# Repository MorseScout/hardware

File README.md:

# Morse Scout custom I/O PCB v1.2

This directory contains the current custom I/O board for Morse Scout. It is
designed for the Elecrow CrowPanel Advanced 7-inch ESP32-P4 host board (PCB
V1.1). PCB revision 1.2 was fabricated from the included Gerber package,
passed bring-up and functional testing, and is used in the current Morse Scout
build.

## Current design

- `J1`: 2x12, 2.54 mm, pin-for-pin connection to Elecrow expansion header
  `J7`. Pins 2, 4, and 6 carry 5 V on the host and are intentionally not
  connected on the custom PCB.
- `J5`-`J7`: three switched TRS Morse-key inputs. Tip and ring are independent
  active-low contacts to ground.
- `ENC1`: rotary encoder A/B signals and push switch.
- `RV1`: 10 kOhm linear volume potentiometer. `R1/C1` form the 1 kOhm/100 nF
  ADC filter.
- `SW1`: active-low sleep/wake button with the 10 kOhm `R2` pull-up.
- `U1`: DS3231 real-time-clock module with battery backup.
- `J8`: four-position HY2.0 I2C connector (`ZX-HY2.0-4PZZ`) between
  the Elecrow board and `U1`.
- `J4`: two-wire Elecrow left-speaker input. Both conductors belong to the
  bridge-tied speaker output; neither conductor is ground.
- `J2`: switched 3.5 mm audio jack.
- `J3`: two-wire internal-speaker connector. Inserting a plug in `J2` opens
  the feed to the internal speaker.

## Opening the project

Use KiCad 10 and open `morse_scout_custom_io_elecrow.kicad_pro`. The project
library tables use `${KIPRJMOD}`, so the included `Libraries` directory is
found without machine-specific paths. A normal KiCad 10 installation is also
required for the standard KiCad symbols, footprints, and 3D models.

The project-local `MorseScout` symbol and footprint libraries contain the
custom parts required to edit and fabricate the board. Their pad and drill
geometry is based on the tested PCB v1.2 design.

## Optional third-party 3D models

This repository does **not** redistribute third-party SamacSys/Component
Search Engine symbols, footprints, or 3D models. The custom symbols and
fabrication-tested footprints needed to edit the project are included. The
footprints contain optional 3D-model references through the
`MORSESCOUT_3DMODEL_DIR` KiCad path variable, but the referenced model files
are intentionally omitted from this public repository.

To enable a fully populated local 3D view, create a directory for the
downloaded models and add this entry in **KiCad > Preferences > Configure
Paths**:

| Name | Value |
| --- | --- |
| `MORSESCOUT_3DMODEL_DIR` | Absolute path to your local model directory |

Use the filenames shown below. If the variable or a model is absent, KiCad may
report a missing model and omit that component from the 3D Viewer. This does
not affect pads, drills, copper, routing, DRC geometry, Gerbers, or other
fabrication data.

Optional vendor CAD data can be obtained from
[SamacSys Component Search Engine](https://componentsearchengine.com/). Search
for the exact manufacturer part number:

| Part | Expected filename | CAD-model search |
| --- | --- | --- |
| Kycon `STX-3120-5B-701C` audio jack | `STX-3120-5B-701C.stp` | [Search](https://componentsearchengine.com/search?term=STX-3120-5B-701C) |
| Bourns `PTV09A-4030F-B103` potentiometer | `PTV09A-4030F-B103.stp` | [Search](https://componentsearchengine.com/search?term=PTV09A-4030F-B103) |
| Omron `B3F-4050` pushbutton | `B3F-4050.stp` | [Search](https://componentsearchengine.com/search?term=B3F-4050) |
| Bourns `PEC11R-4230F-S0024` encoder | `PEC11R-4230F-S0024.stp` | [Search](https://componentsearchengine.com/search?term=PEC11R-4230F-S0024) |
| DS3231 RTC module | `DS3231-RTC-V3.step` | Based on the [DS3231 RTC Module model on GrabCAD](https://grabcad.com/library/ds3231-rtc-module-1) |
| Megastar `ZX-HY2.0-4PZZ` four-position HY2.0 connector | `CONN-TH_4P-P2.00_HX20020-4A_2.step` | [LCSC C7429580](https://www.lcsc.com/product-detail/C7429580.html) |

Availability differs by part: the service may offer a direct download or a
model-request workflow, and an account may be required. Review and accept the
provider's current terms before downloading. Keep downloaded files outside
this repository unless their license expressly permits redistribution.

Do not replace the included footprints merely to obtain a 3D model: the
included pad and drill geometry is the fabrication-tested v1.2 geometry. If an
external footprint is substituted, verify its pad numbers, hole sizes,
spacing, and mechanical clearances before manufacturing.

The fitted encoder is `PEC11R-4230F-S0024`. Its PCB mounting geometry is the
same as the shorter-shaft `PEC11R-4220F-S0024`; the project and sourcing links
use the fitted 4230F manufacturer part number.

## Release files

- KiCad source: `morse_scout_custom_io_elecrow.kicad_sch`,
  `morse_scout_custom_io_elecrow.kicad_pcb`, and
  `morse_scout_custom_io_elecrow.kicad_pro`.
- Tested fabrication package:
  [`Gerbers/v1.2/morse_tutor_custom_io_elecrow-v1.2.zip`](Gerbers/v1.2/morse_tutor_custom_io_elecrow-v1.2.zip).
  The archive filename is retained unchanged because this is the exact package
  used to fabricate and validate PCB v1.2.

Manufacturer part numbers and component values are stored in the schematic
symbol properties. Use the included v1.2 fabrication package when ordering
this tested board revision.

## Validation

Native KiCad 10 validation on 2026-10-28:

- Schematic ERC: 0 errors and 0 warnings.
- PCB routing: complete, with 0 unrouted nets.
- PCB DRC: 20 accepted warnings and 0 unconnected pads. All 20 warnings are
  expected because the four 3.5 mm jack footprints deliberately overhang the
  board edge.
- A PCB fabricated from the v1.2 Gerbers passed the current Morse Scout
  bring-up and functional tests.

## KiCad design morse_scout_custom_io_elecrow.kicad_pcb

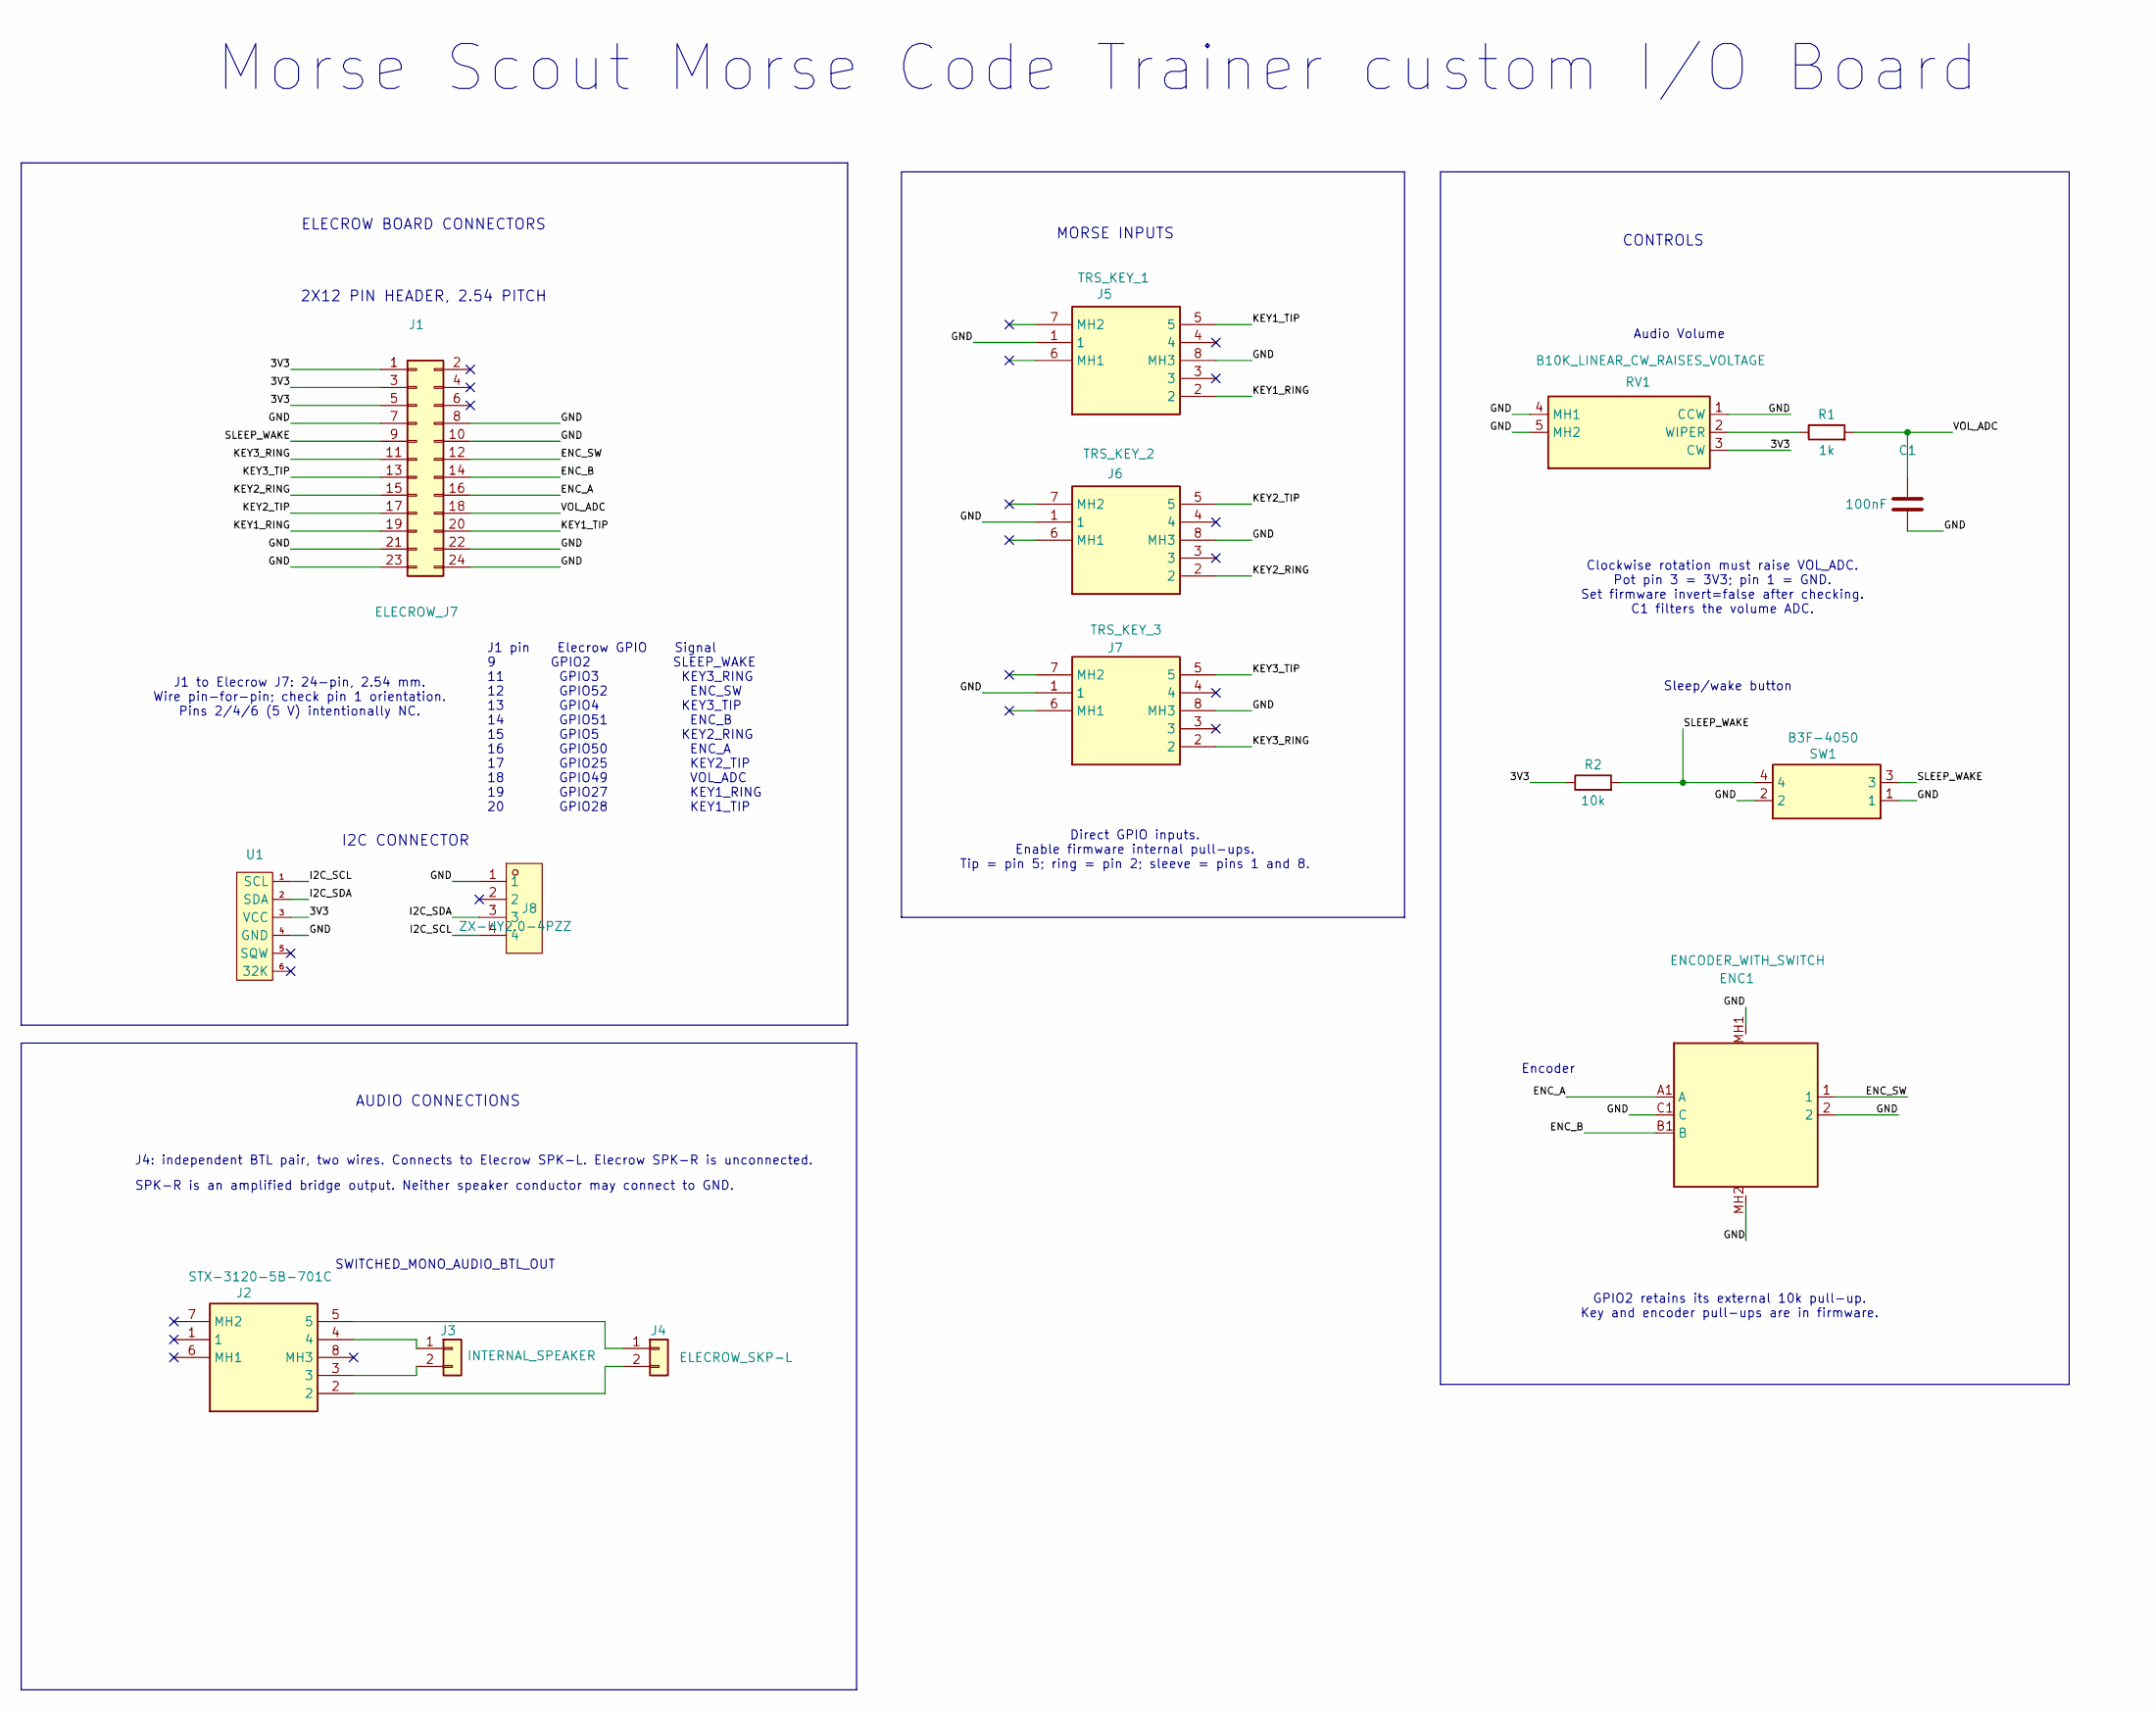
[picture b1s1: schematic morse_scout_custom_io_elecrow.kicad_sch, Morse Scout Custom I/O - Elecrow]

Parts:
C1: 100nF; C_Disc_D5.0mm_W2.5mm_P5.00mm
ENC1: ENCODER_WITH_SWITCH; PEC11R-4230F-S0024; Manufacturer_Part_Number PEC11R-4230F-S0024; Mouser Part Number 652-PEC11R-4230F-S24
J1: ELECROW_J7; IDC-Header_2x12_P2.54mm_Vertical
J2: STX-3120-5B-701C; Manufacturer_Part_Number STX-3120-5B-701C; Mouser Part Number 806-STX-31205B701C
J3: INTERNAL_SPEAKER; JST_PH_B2B-PH-K_1x02_P2.00mm_Vertical
J4: ELECROW_SKP-L; JST_PH_B2B-PH-K_1x02_P2.00mm_Vertical
J5: TRS_KEY_1; STX-3120-5B-701C; Manufacturer_Part_Number STX-3120-5B-701C; Mouser Part Number 806-STX-31205B701C
J6: TRS_KEY_2; STX-3120-5B-701C; Manufacturer_Part_Number STX-3120-5B-701C; Mouser Part Number 806-STX-31205B701C
J7: TRS_KEY_3; STX-3120-5B-701C; Manufacturer_Part_Number STX-3120-5B-701C; Mouser Part Number 806-STX-31205B701C
J8: ZX-HY2.0-4PZZ; CONN-TH_4P-P2.00_HX20020-4A_2; MPN ZX-HY2.0-4PZZ; LCSC Part C7429580
R1: 1k; R_Axial_DIN0204_L3.6mm_D1.6mm_P7.62mm_Horizontal
R2: 10k; R_Axial_DIN0204_L3.6mm_D1.6mm_P7.62mm_Horizontal
RV1: B10K_LINEAR_CW_RAISES_VOLTAGE; PTV09A-4030F-B103; Mouser Part Number 652-PTV09A4030FB103
SW1: B3F-4050
U1: DS3231_RTC_Module

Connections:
/3V3: J1.1, J1.3, J1.5, R2.1, RV1.3 (CW), U1.3 (VCC)
/ENC_A: ENC1.A1 (A), J1.16
/ENC_B: ENC1.B1 (B), J1.14
/ENC_SW: ENC1.1, J1.12
/GND: C1.2, ENC1.2, ENC1.C1 (C), ENC1.MH1, ENC1.MH2, J1.7, J1.8, J1.10, J1.21, J1.22, J1.23, J1.24, J5.1, J5.8 (MH3), J6.1, J6.8 (MH3), J7.1, J7.8 (MH3), J8.1, RV1.1 (CCW), RV1.4 (MH1), RV1.5 (MH2), SW1.1, SW1.2, U1.4 (GND)
/I2C_SCL: J8.4, U1.1 (SCL)
/I2C_SDA: J8.3, U1.2 (SDA)
/KEY1_RING: J1.19, J5.2
/KEY1_TIP: J1.20, J5.5
/KEY2_RING: J1.15, J6.2
/KEY2_TIP: J1.17, J6.5
/KEY3_RING: J1.11, J7.2
/KEY3_TIP: J1.13, J7.5
/SLEEP_WAKE: J1.9, R2.2, SW1.3, SW1.4
/VOL_ADC: C1.1, J1.18, R1.2
unnamed: J2.4, J3.1
unnamed: J2.3, J3.2
unnamed: J2.5, J4.1
unnamed: J2.2, J4.2
unnamed: R1.1, RV1.2 (WIPER)

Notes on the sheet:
MORSE INPUTS
Direct GPIO inputs. Enable firmware internal pull-ups. Tip = pin 5; ring = pin 2; sleeve = pins 1 and 8.
I2C CONNECTOR
Audio Volume
SPK-R is an amplified bridge output. Neither speaker conductor may connect to GND.
Sleep/wake button
ELECROW BOARD CONNECTORS
SWITCHED_MONO_AUDIO_BTL_OUT
CONTROLS
J4: independent BTL pair, two wires. Connects to Elecrow SPK-L. Elecrow SPK-R is unconnected.
Morse Scout Morse Code Trainer custom I/O Board
Encoder
GPIO2 retains its external 10k pull-up. Key and encoder pull-ups are in firmware.
AUDIO CONNECTIONS
J1 to Elecrow J7: 24-pin, 2.54 mm. Wire pin-for-pin; check pin 1 orientation. Pins 2/4/6 (5 V) intentionally NC.
2X12 PIN HEADER, 2.54 PITCH
Clockwise rotation must raise VOL_ADC. Pot pin 3 = 3V3; pin 1 = GND. Set firmware invert=false after checking. C1 filters the volume ADC.
J1 pin Elecrow GPIO Signal 9 GPIO2 SLEEP_WAKE 11 GPIO3 KEY3_RING 12 GPIO52 ENC_SW 13 GPIO4 KEY3_TIP 14 GPIO51 ENC_B 15 GPIO5 KEY2_RING 16 GPIO50 ENC_A 17 GPIO25 KEY2_TIP 18 GPIO49 VOL_ADC 19 GPIO27 KEY1_RING 20 GPIO28 KEY1_TIP

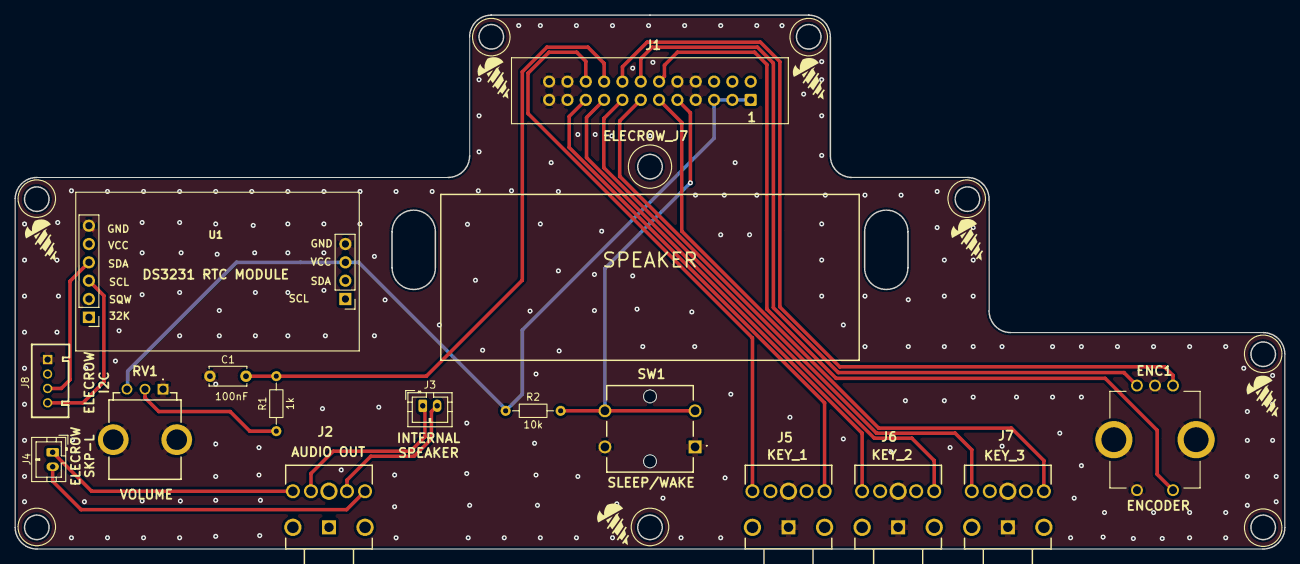
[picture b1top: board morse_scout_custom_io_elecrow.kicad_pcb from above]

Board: 2 copper layers, 176.0 x 74.0 mm, 15 parts (1 on the bottom side), 20 nets.
